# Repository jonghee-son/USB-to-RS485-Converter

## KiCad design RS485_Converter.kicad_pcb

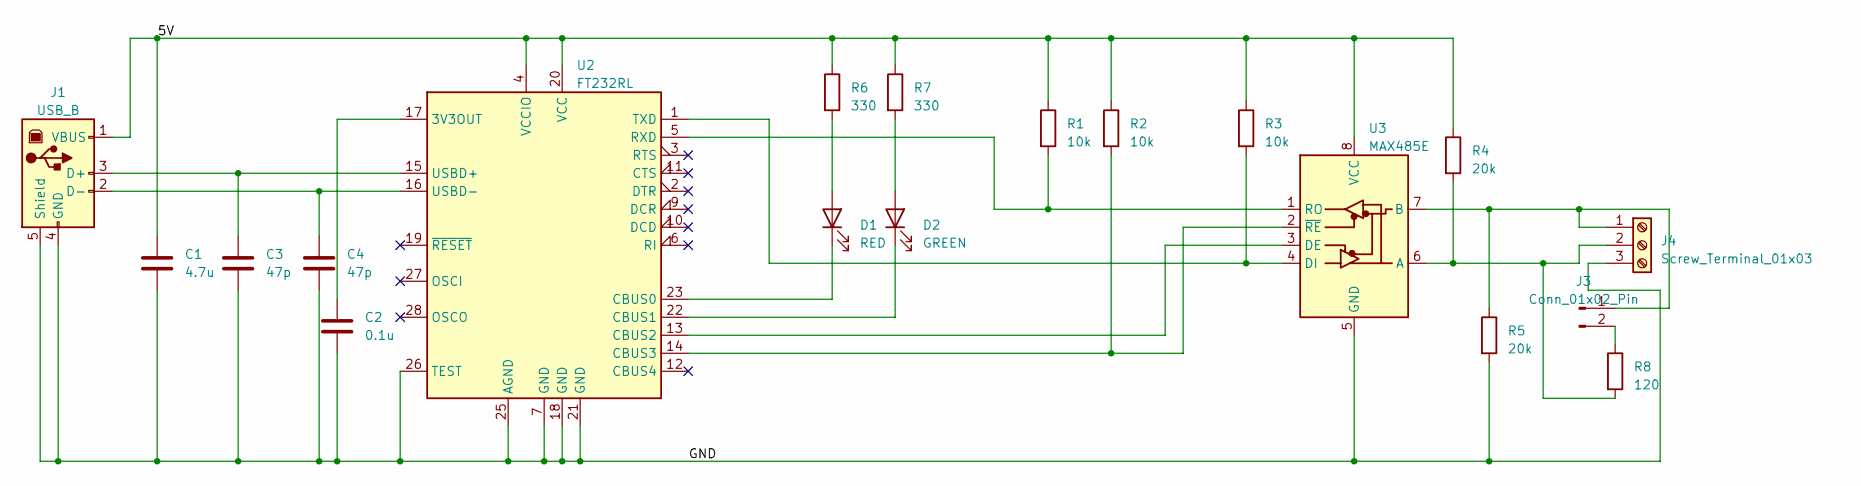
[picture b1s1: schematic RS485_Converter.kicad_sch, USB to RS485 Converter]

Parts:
C1: 4.7u; C_Disc_D4.7mm_W2.5mm_P5.00mm
C2: 0.1u; C_Disc_D4.7mm_W2.5mm_P5.00mm
C3, C4: 47p; C_Disc_D4.7mm_W2.5mm_P5.00mm
D1: RED; LED_D5.0mm
D2: GREEN; LED_D5.0mm
J1: USB_B; USB_B_Lumberg_2411_02_Horizontal
J3: Conn_01x02_Pin; PinHeader_1x02_P2.54mm_Vertical
J4: Screw_Terminal_01x03; TerminalBlock_MetzConnect_Type059_RT06303HBWC_1x03_P3.50mm_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
R1, R2, R3: 10k; R_Axial_DIN0207_L6.3mm_D2.5mm_P10.16mm_Horizontal
R4, R5: 20k; R_Axial_DIN0207_L6.3mm_D2.5mm_P10.16mm_Horizontal
R6, R7: 330; R_Axial_DIN0207_L6.3mm_D2.5mm_P10.16mm_Horizontal
R8: 120; R_Axial_DIN0207_L6.3mm_D2.5mm_P10.16mm_Horizontal
U2: FT232RL; SSOP-28_5.3x10.2mm_P0.65mm
U3: MAX485E; DIP-8_W7.62mm_Socket

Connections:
/5V: C1.1, J1.1 (VBUS), R1.1, R2.1, R3.1, R4.1, R6.1, R7.1, U2.4 (VCCIO), U2.20 (VCC), U3.8 (VCC)
/GND: C1.2, C2.2, C3.2, C4.2, J1.4 (GND), J1.5 (Shield), J4.3, R5.2, U2.7 (GND), U2.18 (GND), U2.21 (GND), U2.25 (AGND), U2.26 (TEST), U3.5 (GND)
unnamed: D1.2 (A), R6.2
unnamed: D1.1 (K), U2.23 (CBUS0)
unnamed: D2.2 (A), R7.2
unnamed: D2.1 (K), U2.22 (CBUS1)
unnamed: C3.1, J1.3 (D+), U2.15 (USBD+)
unnamed: C4.1, J1.2 (D-), U2.16 (USBD-)
unnamed: J3.1, J4.1, R5.1, U3.7 (B)
unnamed: J3.2, R8.1
unnamed: J4.2, R4.2, R8.2, U3.6 (A)
unnamed: C2.1, U2.17 (3V3OUT)
unnamed: U2.13 (CBUS2), U3.3 (DE)
unnamed: R2.2, U2.14 (CBUS3), U3.2 (~RE)
unnamed: R1.2, U2.5 (RXD), U3.1 (RO)
unnamed: R3.2, U2.1 (TXD), U3.4 (DI)

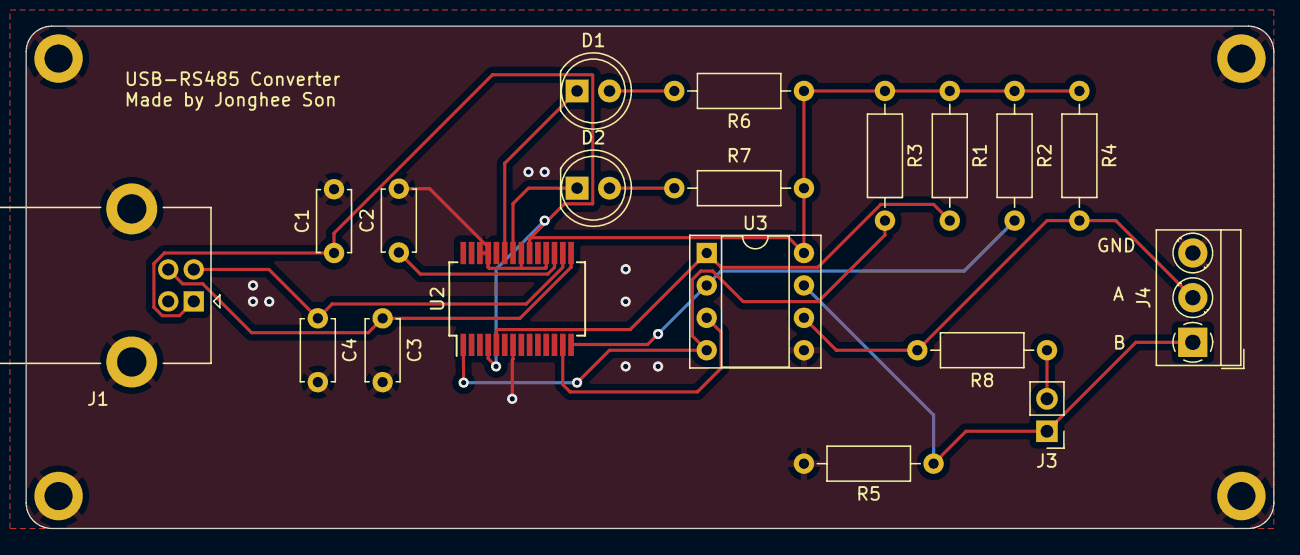
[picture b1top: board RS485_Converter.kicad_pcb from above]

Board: 2 copper layers, 97.8 x 39.4 mm, 19 parts (0 on the bottom side), 16 nets.

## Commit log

2024-03-15 Fixed FT232RL connection
